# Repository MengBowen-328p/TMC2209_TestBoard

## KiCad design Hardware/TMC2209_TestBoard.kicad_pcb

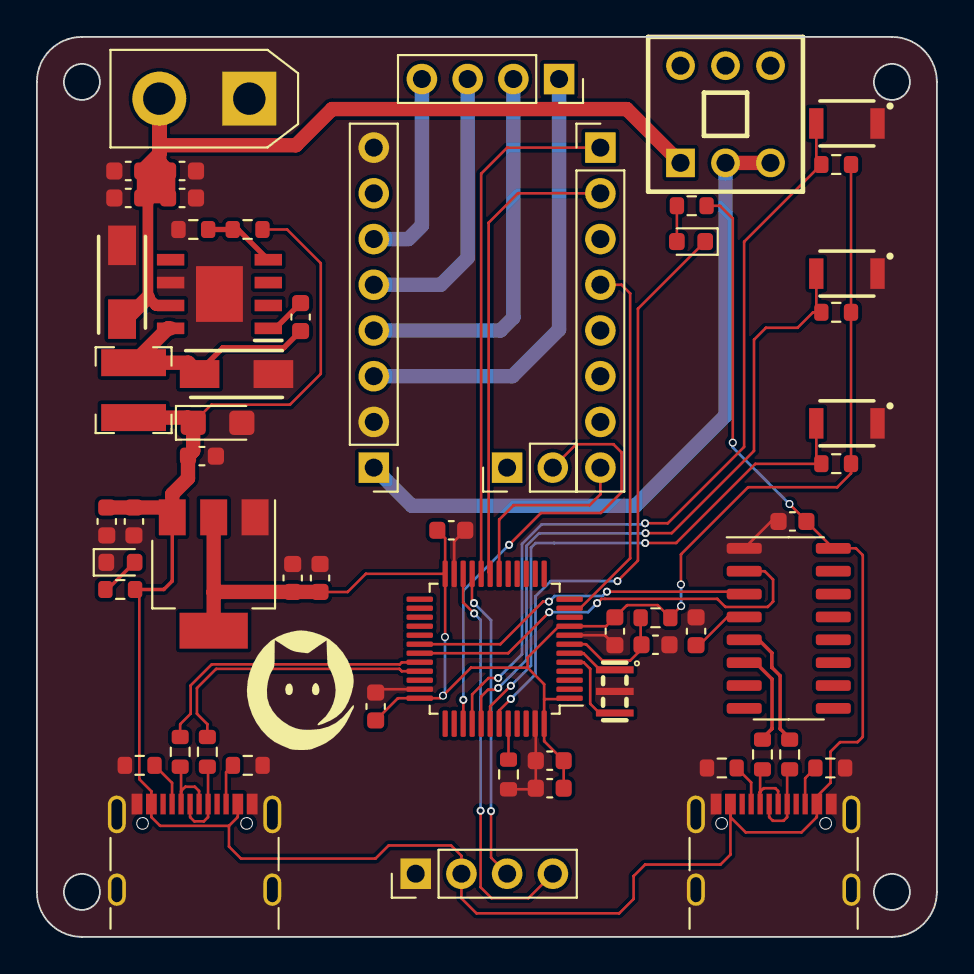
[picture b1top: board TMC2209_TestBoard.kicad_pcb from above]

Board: 2 copper layers, 50.0 x 50.0 mm, 58 parts (0 on the bottom side), 44 nets.

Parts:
C1, C2, C3, C4, C5, C7, C8, C9: 0.1uF; C_0603_1608Metric
C6: 1uF; C_0603_1608Metric
C10, C11, C13, C14, C15: 4.7uF; C_0603_1608Metric
C12: 470uF; CP_EIA-3216-10_Kemet-I
C16, C17, C18, C19: 10uF; C_0603_1608Metric
D1, D4: Power_LED; LED_0603_1608Metric
D2, D3: SS54; DIOM5126X245N
IC1: TPS5450DDAR; SOIC127P600X170-9N
J1, J2: Conn_01x08_Pin; PinHeader_1x08_P2.54mm_Vertical
J3: Conn_01x02_Pin; PinHeader_1x02_P2.54mm_Vertical
J4: Conn_01x04_Socket; PinHeader_1x04_P2.54mm_Vertical
J5, J6: USB_C_Receptacle; USB_C_Receptacle_GCT_USB4105-xx-A_16P_TopMnt_Horizontal
J7: Conn_01x02_Pin; AMASS_XT30UPB-M_1x02_P5.0mm_Vertical
J8: Conn_01x04_Socket; PinSocket_1x04_P2.54mm_Vertical
L1: 15uH; L_Bourns-SRN4018
R1, R4, R5, R6, R7, R8, R14: 10K; R_0603_1608Metric
R2: CSTCE8M00G55-R0; CSTCE12M0G55-R0
R3, R12, R13, R17, R18: 22R; R_0603_1608Metric
R9: 3.16K; R_0603_1608Metric
R10, R11, R15, R16: 5K1; R_0603_1608Metric
S1, S2, S3: B3U-1000P
SW1: XKB8585-Z-190; SW-TH_6P-L8.6-W8.6-P2.50-LS5.4
U1: STM32F103C8Tx; LQFP-48_7x7mm_P0.5mm
U2: CH340C; SOIC-16_3.9x9.9mm_P1.27mm
U3: AMS1117-3.3; SOT-223-3_TabPin2

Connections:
+3.3V: C1.1, C2.1, C3.1, C5.1, C6.1, C18.1, C19.1, R1.1, R5.1, R6.1, R7.1, U1.1 (VBAT), U1.9 (VDDA), U1.24 (VDD), U1.36 (VDD), U1.48 (VDD), U3.2 (VO)
+5V: C8.1, C10.1, C12.1, C16.1, C17.1, J4.2, J5.A4 (VBUS), J5.A9 (VBUS), J5.B4 (VBUS), J5.B9 (VBUS), J6.A4 (VBUS), J6.A9 (VBUS), J6.B4 (VBUS), J6.B9 (VBUS), L1.2, R4.1, R8.2, R14.1, U2.16 (VCC), U3.3 (VI)
/Driver_DIR: J2.1, U1.20 (PB2)
/Driver_Diag: J3.2, U1.39 (PB3)
/Driver_EN: J2.8, U1.18 (PB0)
/Driver_STP: J2.2, U1.19 (PB1)
/KEY_1: R5.2, S1.2 (A), U1.40 (PB4)
/KEY_2: R6.2, S2.2 (A), U1.41 (PB5)
/KEY_3: R7.2, S3.2 (A), U1.42 (PB6)
/LED: D1.1 (K), U1.43 (PB7)
/OA1: J1.4, J8.2
/OA2: J1.3, J8.1
/OB1: J1.5, J8.3
/OB2: J1.6, J8.4
/OLED_SCL: J4.3, U1.21 (PB10)
/OLED_SDA: J4.4, U1.22 (PB11)
/USART1_RX: U1.31 (PA10), U2.2 (TXD)
/USART1_TX: U1.30 (PA9), U2.3 (RXD)
/USART2_TX: J2.4, U1.11 (PA1)
/USB1_DN: R17.1, U1.32 (PA11)
/USB1_DP: R18.1, U1.33 (PA12)
/USB_UART_DN: R12.1, U2.6 (UD-)
/USB_UART_DP: R13.1, U2.5 (UD+)
GND: C1.2, C2.2, C3.2, C4.2, C5.2, C6.2, C7.2, C8.2, C10.2, C11.2, C12.2, C13.2, C14.2, C15.2, C16.2, C17.2, C18.2, C19.2, D2.2 (A), D3.2 (A), D4.1 (K), IC1.6 (GND), IC1.9 (EP), J1.2, J1.8, J4.1, J5.A1 (GND), J5.A12 (GND), J5.B1 (GND), J5.B12 (GND), J5.S1 (SHIELD), J6.A1 (GND), J6.A12 (GND), J6.B1 (GND), J6.B12 (GND), J6.S1 (SHIELD), J7.1, R2.2, R3.1, R9.1, R10.1, R11.1, R15.1, R16.1, S1.1 (K), S2.1 (K), S3.1 (K), U1.8 (VSSA), U1.23 (VSS), U1.35 (VSS), U1.47 (VSS), U2.1 (GND), U3.1 (GND)
unnamed: D1.2 (A), R4.2
unnamed: C9.1, D2.1 (K), IC1.8 (PH), L1.1
unnamed: C11.1, C13.1, C14.1, C15.1, D3.1 (K), IC1.7 (VIN), J7.2, SW1.1
unnamed: D4.2 (A), R14.2
unnamed: C9.2, IC1.1 (BOOT)
unnamed: IC1.4 (VSENSE), R8.1, R9.2
unnamed: J5.A5 (CC1), R10.2
unnamed: J5.B5 (CC2), R11.2
unnamed: J5.A6 (D+), J5.B6 (D+), R13.2
unnamed: J5.A7 (D-), J5.B7 (D-), R12.2
unnamed: J6.A5 (CC1), R15.2
unnamed: J6.B5 (CC2), R16.2
unnamed: J6.A6 (D+), J6.B6 (D+), R18.2
unnamed: J6.A7 (D-), J6.B7 (D-), R17.2
unnamed: R3.2, U1.44 (BOOT0)
unnamed: C4.1, R1.2, U1.7 (NRST)
unnamed: R2.3, U1.5 (PD0)
unnamed: R2.1, U1.6 (PD1)
unnamed: C7.1, U2.4 (V3)
VCC: J1.1, SW1.2, SW1.3

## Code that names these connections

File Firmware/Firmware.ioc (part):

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Mcu.Name=STM32F103C(4-6)Tx
Mcu.Package=LQFP48
Mcu.UserName=STM32F103C6Tx
PA10.Mode=Asynchronous
PA10.Signal=USART1_RX
PA11.Mode=Device
PA11.Signal=USB_DM
PA12.Mode=Device
PA12.Signal=USB_DP
PA13.Mode=Serial_Wire
PA13.Signal=SYS_JTMS-SWDIO
PA14.Mode=Serial_Wire
PA14.Signal=SYS_JTCK-SWCLK
PA9.Mode=Asynchronous
PA9.Signal=USART1_TX
PB0.GPIOParameters=GPIO_Label
PB0.GPIO_Label=Driver_EN
PB0.Signal=GPIO_Output
PB1.GPIOParameters=GPIO_Label
PB1.GPIO_Label=Driver_STP
PB1.Signal=GPIO_Output
PB2.GPIOParameters=GPIO_Label
PB2.GPIO_Label=Driver_DIR
PB2.Signal=GPIO_Output
PD0-OSC_IN.Mode=HSE-External-Oscillator
PD0-OSC_IN.Signal=RCC_OSC_IN
PD1-OSC_OUT.Mode=HSE-External-Oscillator
PD1-OSC_OUT.Signal=RCC_OSC_OUT
RCC.HSE_VALUE=12000000
RCC.SYSCLKFreq_VALUE=72000000
RCC.SYSCLKSource=RCC_SYSCLKSOURCE_PLLCLK
board=custom

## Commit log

2023-08-28 Init Repo
2023-09-06 Update Basic Firmware
2023-09-07 Firmware V1.1
2023-09-16 Update Uart Driver
